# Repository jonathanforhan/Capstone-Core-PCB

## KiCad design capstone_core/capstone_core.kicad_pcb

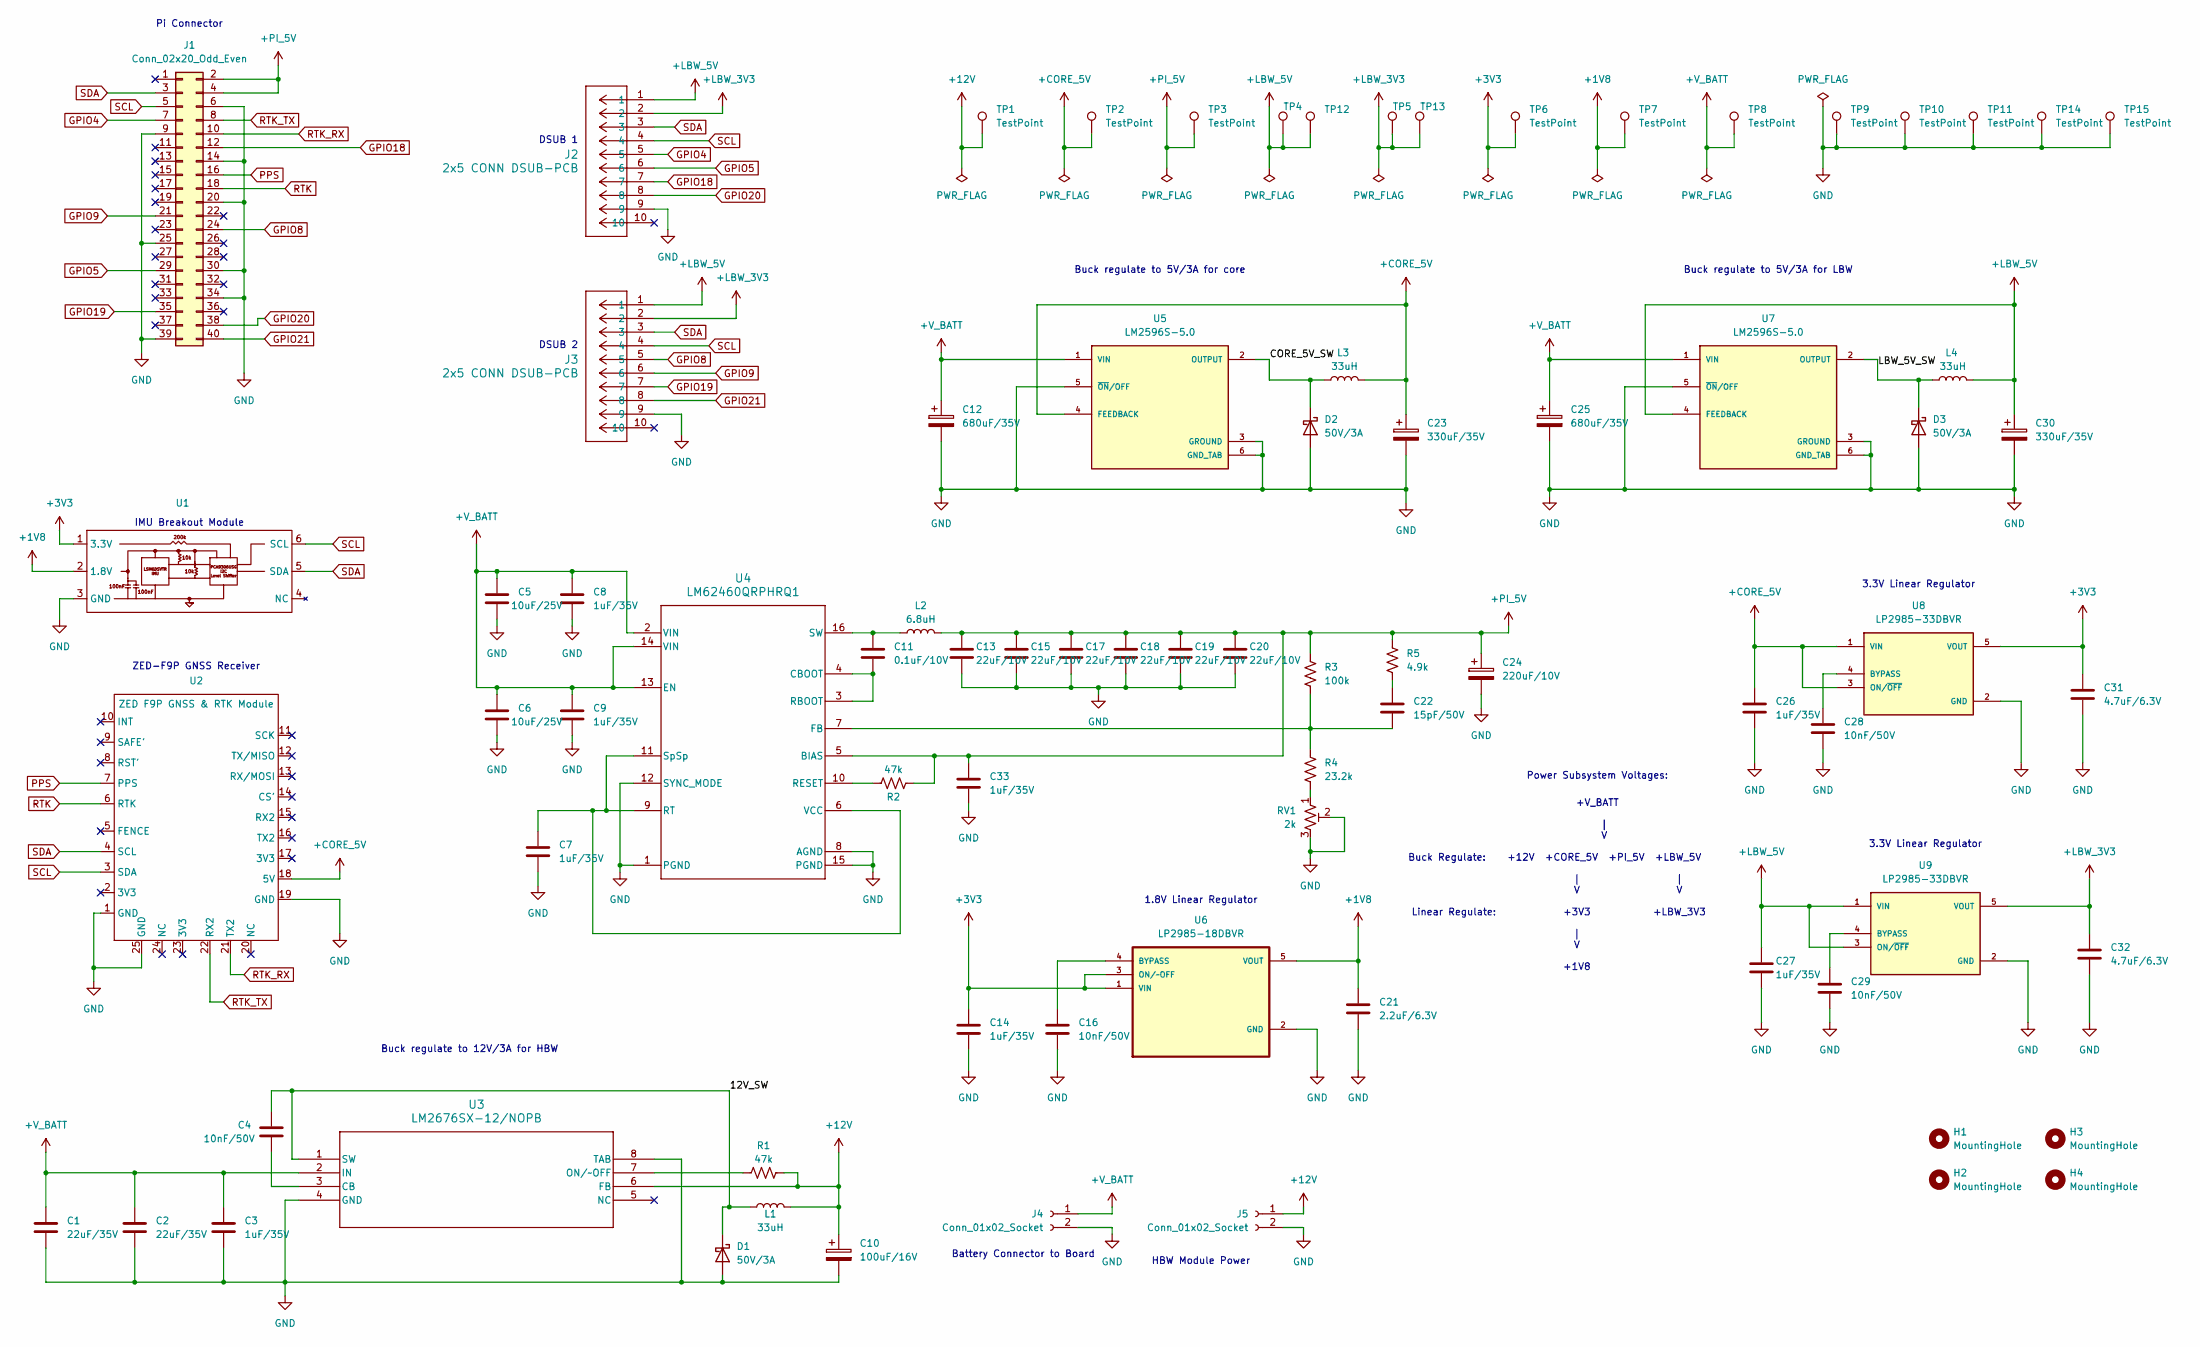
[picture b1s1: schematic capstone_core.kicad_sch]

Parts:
C1, C2: 22uF/35V; C_0805_2012Metric_Pad1.18x1.45mm_HandSolder
C3: 1uF/35V; C_0805_2012Metric_Pad1.18x1.45mm_HandSolder
C4, C16, C28, C29: 10nF/50V; C_0603_1608Metric_Pad1.08x0.95mm_HandSolder
C5, C6: 10uF/25V; C_0805_2012Metric_Pad1.18x1.45mm_HandSolder
C7, C8, C9, C14, C26, C27, C33: 1uF/35V; C_0603_1608Metric_Pad1.08x0.95mm_HandSolder
C10: 100uF/16V; CAP_100uF_16V_16SEPC100M_TSS
C11: 0.1uF/10V; C_0603_1608Metric_Pad1.08x0.95mm_HandSolder
C12, C25: 680uF/35V; CAP_680uF_35V_EEHZS1V681UV
C13, C15, C17, C18, C19, C20: 22uF/10V; C_0805_2012Metric_Pad1.18x1.45mm_HandSolder
C21: 2.2uF/6.3V; C_0603_1608Metric_Pad1.08x0.95mm_HandSolder
C22: 15pF/50V; C_0603_1608Metric_Pad1.08x0.95mm_HandSolder
C23, C30: 330uF/35V; CAP_330uF_35V_UCL1V331MNL1GS-L
C24: 220uF/10V; CAP_100uF_16V_16SEPC100M_TSS
C31, C32: 4.7uF/6.3V; C_0603_1608Metric_Pad1.08x0.95mm_HandSolder
D1, D2, D3: 50V/3A; D_SMC_Handsoldering
H1, H2, H3, H4: MountingHole; MountingHole_2.7mm
J1: Conn_02x20_Odd_Even; PI_Connector
J2, J3: 2x5 CONN DSUB-PCB; 2x5_CONN_P100X100-RIBBON_TYC
J4, J5: Conn_01x02_Socket; 1x2_CONN_SD-43650-010_02_MOL
L1, L3, L4: 33uH; IND_33uH_3A_CDRH127NP-330MC
L2: 6.8uH; IND_6.8uH_CB_DRA127
R1, R2: 47k; R_0603_1608Metric_Pad0.98x0.95mm_HandSolder
R3: 100k; R_0603_1608Metric_Pad0.98x0.95mm_HandSolder
R4: 23.2k; R_0603_1608Metric_Pad0.98x0.95mm_HandSolder
R5: 4.9k; R_0603_1608Metric_Pad0.98x0.95mm_HandSolder
RV1: 2k; POT_2k_PV36W202C01B00
TP1, TP2, TP3, TP5, TP6, TP7, TP8, TP9, TP10, TP11, TP12, TP13, TP14, TP15: TestPoint; testpoint_1.0mm_hole
TP4: +LBW_3V3; testpoint_1.0mm_hole
U1: IMU_Breakout_Module
U2: ZED F9P GNSS & RTK Module; ZED-F9P
U3: LM2676SX-12/NOPB; LM2676SX-12-L
U4: LM62460QRPHRQ1
U5, U7: LM2596S-5.0; LM2596S-5; PARTREV E; DigiKey_Part_Number LM2596S-5.0/NOPB-ND
U6: LP2985-18DBVR; DigiKey_Part_Number 296-18474-1-ND
U8, U9: LP2985-33DBVR; PARTREV O; DigiKey_Part_Number 296-18476-1-ND

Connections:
+1V8: C21.1, TP7.1, U1.2 (1.8V), U6.5 (VOUT)
+3V3: C14.1, C31.1, TP6.1, U1.1 (3.3V), U6.1 (VIN), U6.3 (ON/~OFF), U8.5 (VOUT)
+12V: C10.1, J5.1, L1.2, R1.1, TP1.1, U3.6 (FB)
+CORE_5V: C23.1, C26.1, L3.2, TP2.1, U2.18 (5V), U5.4 (FEEDBACK), U8.1 (VIN), U8.3 (ON/~OFF)
+LBW_3V3: C32.1, J2.2, J3.2, TP5.1, TP13.1, U9.5 (VOUT)
+LBW_5V: C27.1, C30.1, J2.1, J3.1, L4.2, TP4.1, TP12.1, U7.4 (FEEDBACK), U9.1 (VIN), U9.3 (ON/~OFF)
+PI_5V: C13.1, C15.1, C17.1, C18.1, C19.1, C20.1, C24.1, C33.1, J1.2, J1.4, L2.2, R2.2, R3.1, R5.1, TP3.1, U4.5 (BIAS)
+V_BATT: C1.1, C2.1, C3.1, C5.1, C6.1, C8.1, C9.1, C12.1, C25.1, J4.1, TP8.1, U3.2 (IN), U4.2 (VIN), U4.13 (EN), U4.14 (VIN), U5.1 (VIN), U7.1 (VIN)
/12V_SW: C4.1, D1.1 (K), L1.1, U3.1 (SW)
/CORE_5V_SW: D2.1 (K), L3.1, U5.2 (OUTPUT)
/LBW_5V_SW: D3.1 (K), L4.1, U7.2 (OUTPUT)
GND: C1.2, C2.2, C3.2, C5.2, C6.2, C7.2, C8.2, C9.2, C10.2, C12.2, C13.2, C14.2, C15.2, C16.2, C17.2, C18.2, C19.2, C20.2, C21.2, C23.2, C24.2, C25.2, C26.2, C27.2, C28.2, C29.2, C30.2, C31.2, C32.2, C33.2, D1.2 (A), D2.2 (A), D3.2 (A), J1.6, J1.9, J1.14, J1.20, J1.25, J1.30, J1.34, J1.39, J2.9, J3.9, J4.2, J5.2, RV1.2, RV1.3, TP9.1, TP10.1, TP11.1, TP14.1, TP15.1, U1.3 (GND), U2.1 (GND), U2.19 (GND), U2.25 (GND), U3.4 (GND), U3.8 (TAB), U4.1 (PGND), U4.8 (AGND), U4.12 (SYNC_MODE), U4.15 (PGND), U5.3 (GROUND), U5.5 (~ON/OFF), U5.6 (GND_TAB), U6.2 (GND), U7.3 (GROUND), U7.5 (~ON/OFF), U7.6 (GND_TAB), U8.2 (GND), U9.2 (GND)
GPIO4: J1.7, J2.5
GPIO5: J1.29, J2.6
GPIO8: J1.24, J3.5
GPIO9: J1.21, J3.6
GPIO18: J1.12, J2.7
GPIO19: J1.35, J3.7
GPIO20: J1.38, J2.8
GPIO21: J1.40, J3.8
unnamed: C22.1, R5.2
unnamed: R4.2, RV1.1
unnamed: C4.2, U3.3 (CB)
unnamed: R1.2, U3.7 (ON/~OFF)
unnamed: C11.2, U4.3 (RBOOT), U4.4 (CBOOT)
unnamed: C22.2, R3.2, R4.1, U4.7 (FB)
unnamed: R2.1, U4.10 (RESET)
unnamed: C7.1, U4.6 (VCC), U4.9 (RT), U4.11 (SpSp)
unnamed: C11.1, L2.1, U4.16 (SW)
unnamed: C16.1, U6.4 (BYPASS)
unnamed: C28.1, U8.4 (BYPASS)
unnamed: C29.1, U9.4 (BYPASS)
PPS: J1.16, U2.7 (PPS)
RTK: J1.18, U2.6 (RTK)
RTK_RX: J1.10, U2.21 (TX2)
RTK_TX: J1.8, U2.22 (RX2)
SCL: J1.5, J2.4, J3.4, U1.6 (SCL), U2.3 (SDA)
SDA: J1.3, J2.3, J3.3, U1.5 (SDA), U2.4 (SCL)

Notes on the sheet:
3.3V Linear Regulator
| V
Buck regulate to 5V/3A for LBW
ZED-F9P GNSS Receiver
IMU Breakout Module
+1V8
Buck regulate to 12V/3A for HBW
DSUB 2
Battery Connector to Board
+LBW_3V3
Pi Connector
DSUB 1
Buck Regulate:
HBW Module Power
+12V +CORE_5V +PI_5V +LBW_5V
Buck regulate to 5V/3A for core
+V_BATT
Power Subsystem Voltages:
Linear Regulate:
+3V3
1.8V Linear Regulator

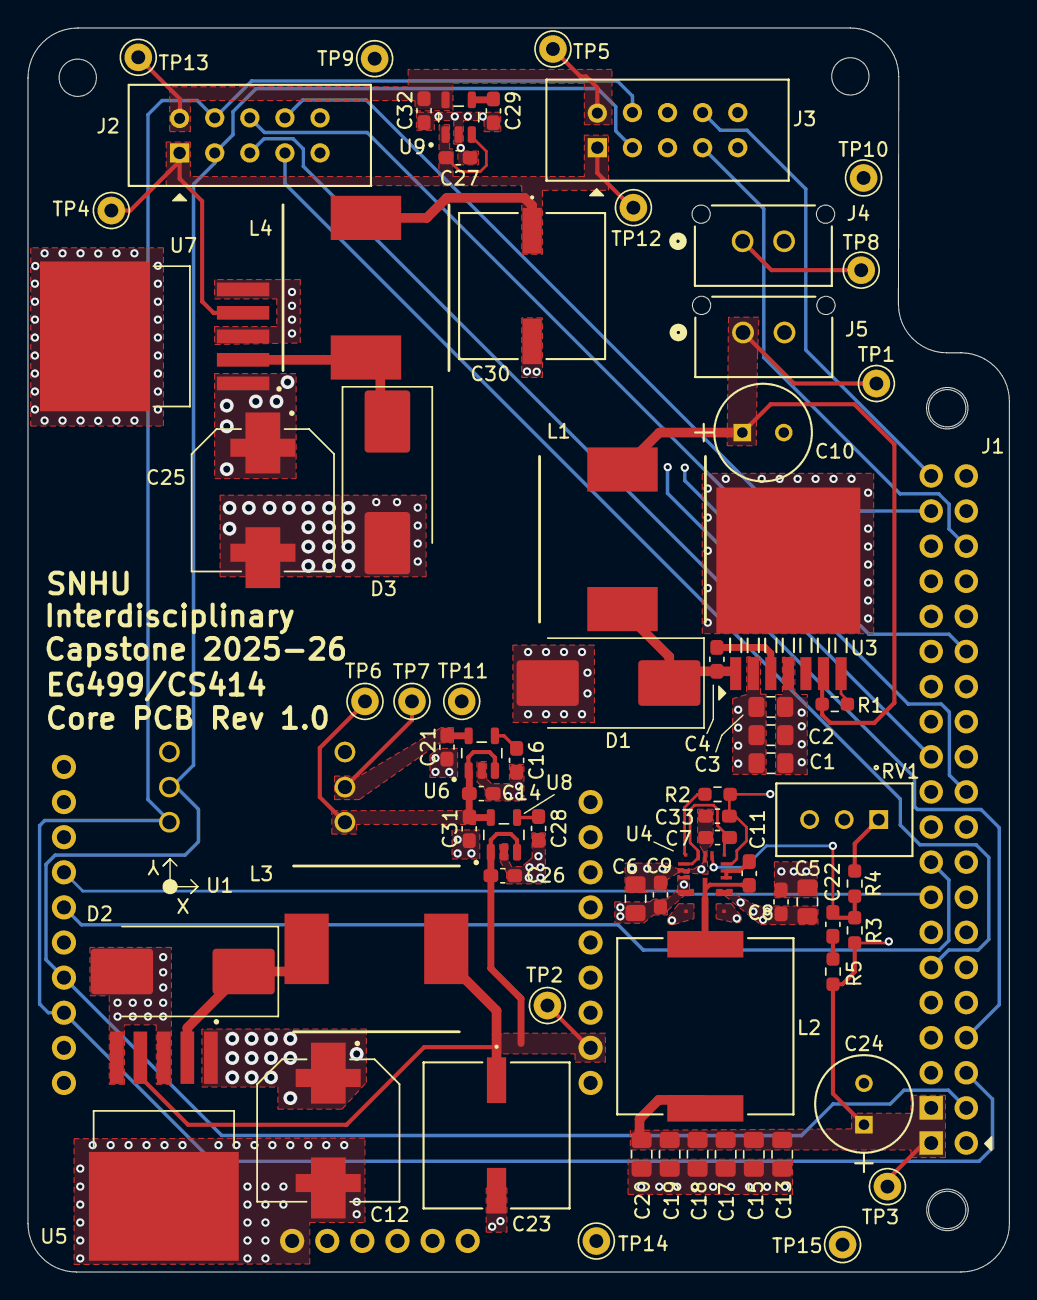
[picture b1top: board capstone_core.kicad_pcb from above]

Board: 4 copper layers, 71.0 x 90.0 mm, 79 parts (1 on the bottom side), 38 nets.

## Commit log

2025-11-25 adding hierarchical blocks and connectors
2025-12-02 putting all footprints in Capstone Footprints Library
2026-02-08 Core PCB. Revision 1.0
2026-02-09 Added 3D models, changed C12 and C25 to shorter capacitor. Fixed library paths to be relative to KiCad project directory
